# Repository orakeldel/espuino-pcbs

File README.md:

PCBs for espuino.

Note: Work in progress, no working prototyp yet.

Mainboard:
- Board with esp32 wrover, connectors for 6 buttons and led ring, lifepo battery charger, speaker (mono+stereo) and headphones.

Capabutton:
- Capacitive button with led and solder connector

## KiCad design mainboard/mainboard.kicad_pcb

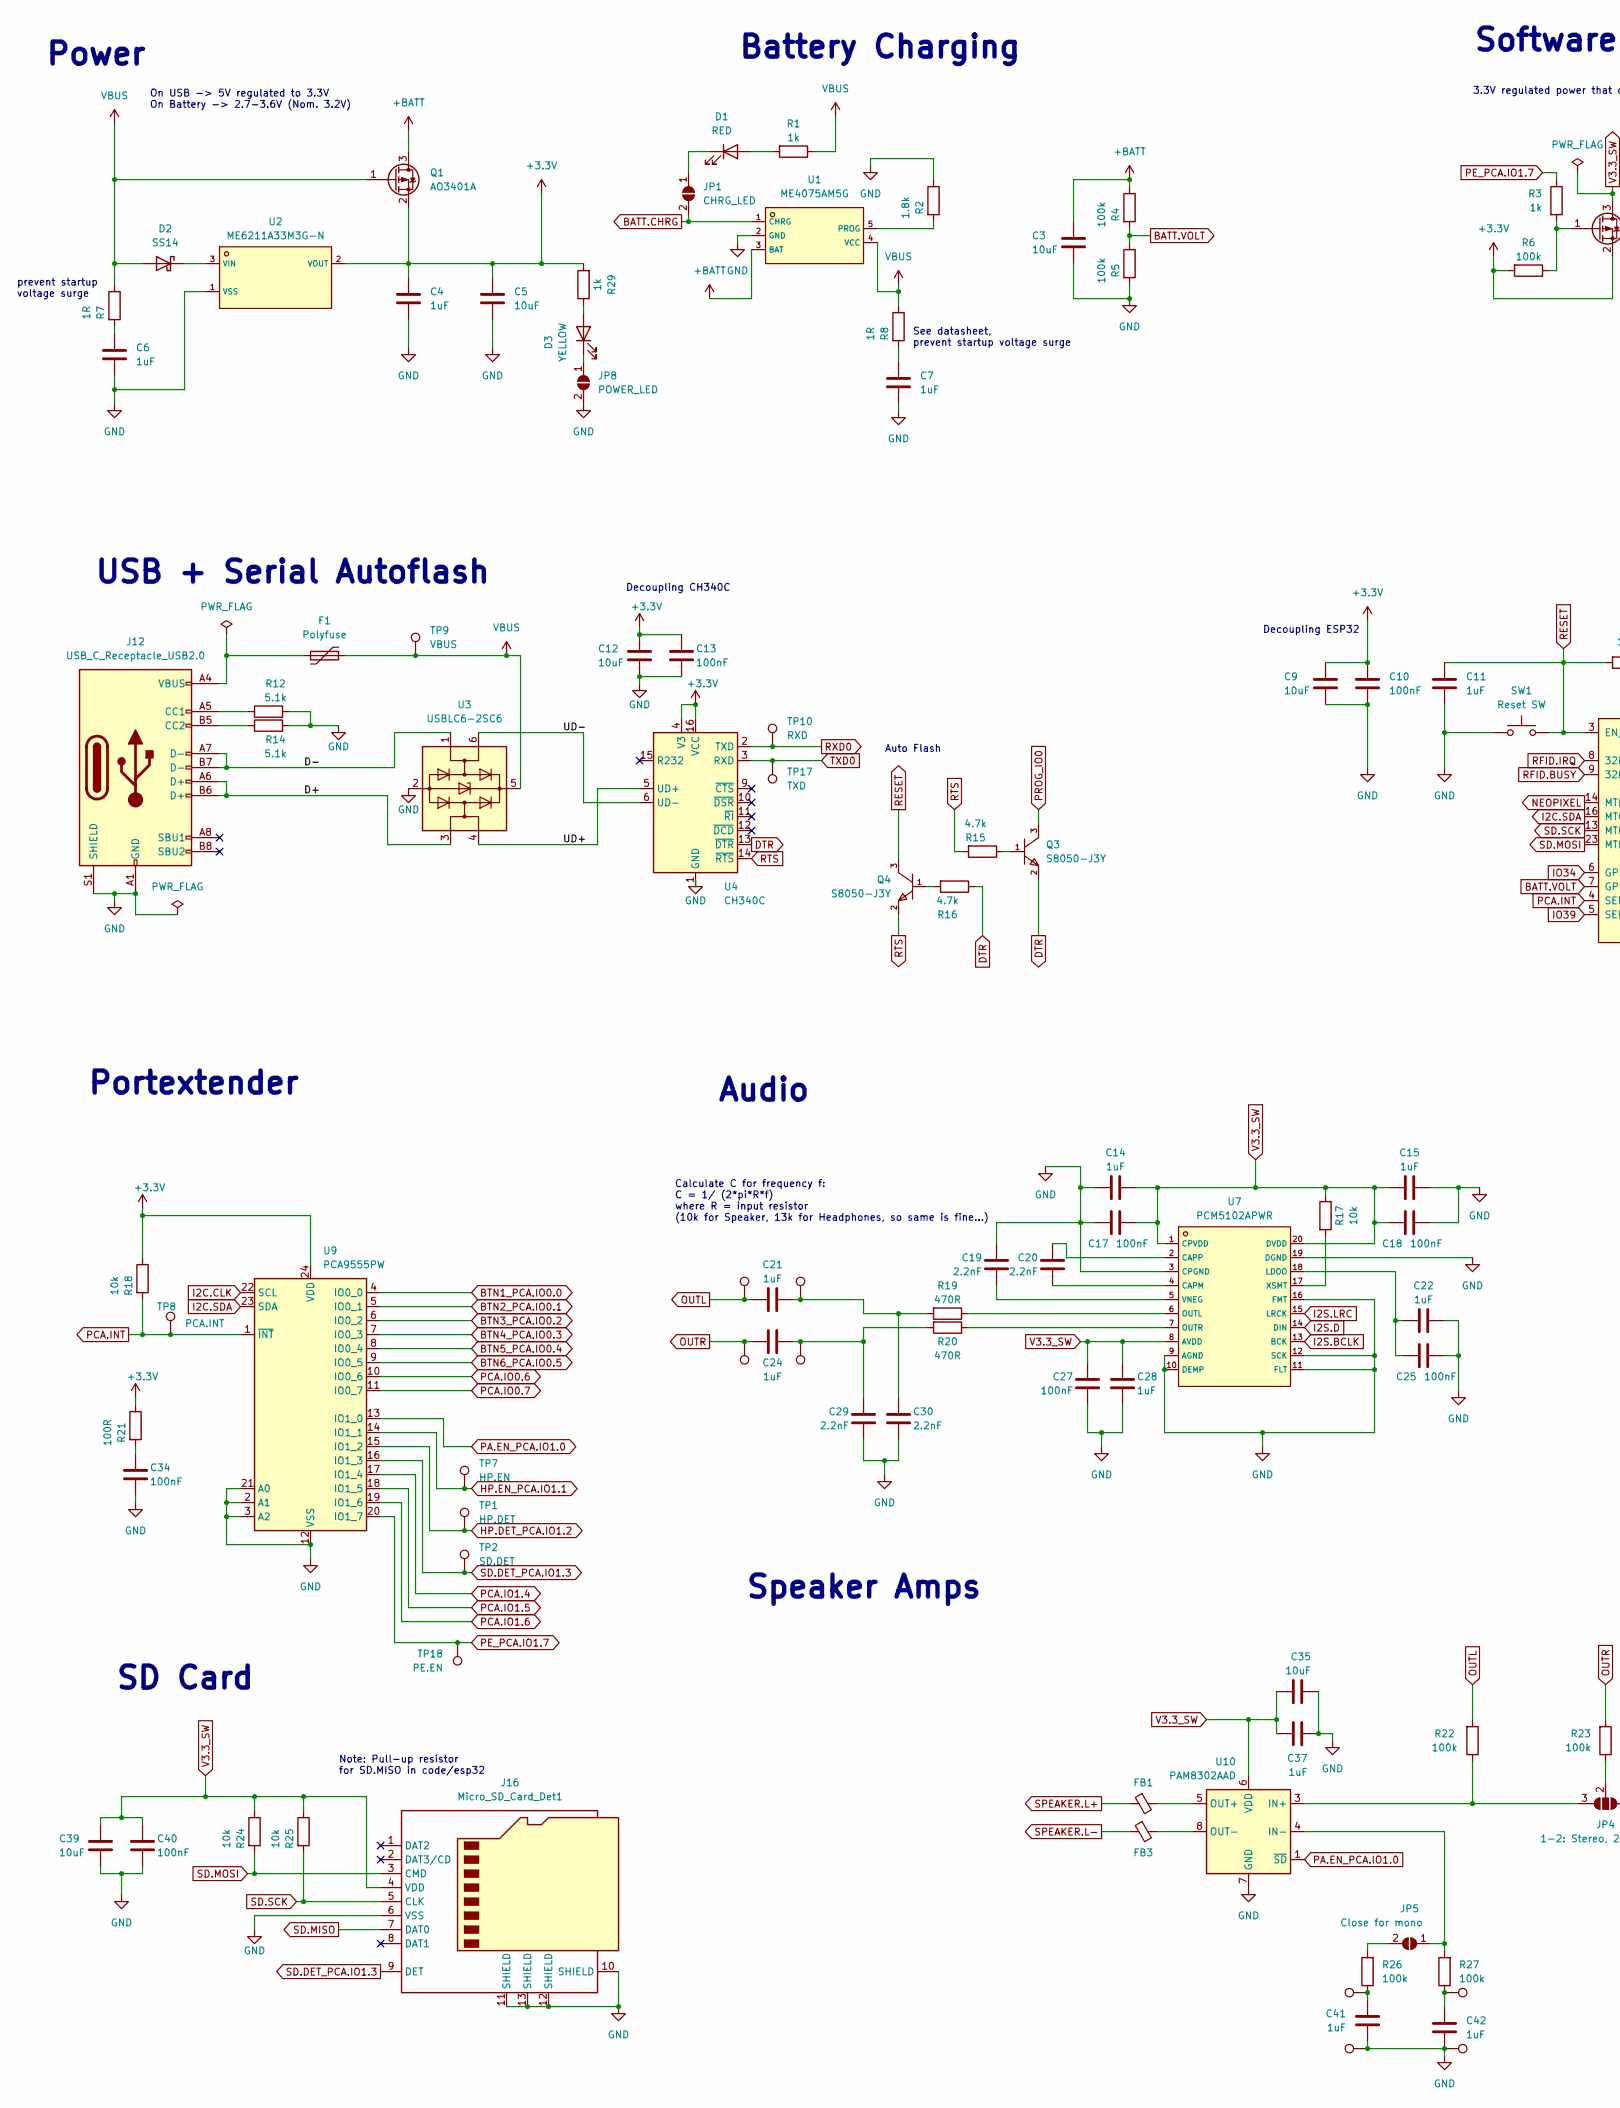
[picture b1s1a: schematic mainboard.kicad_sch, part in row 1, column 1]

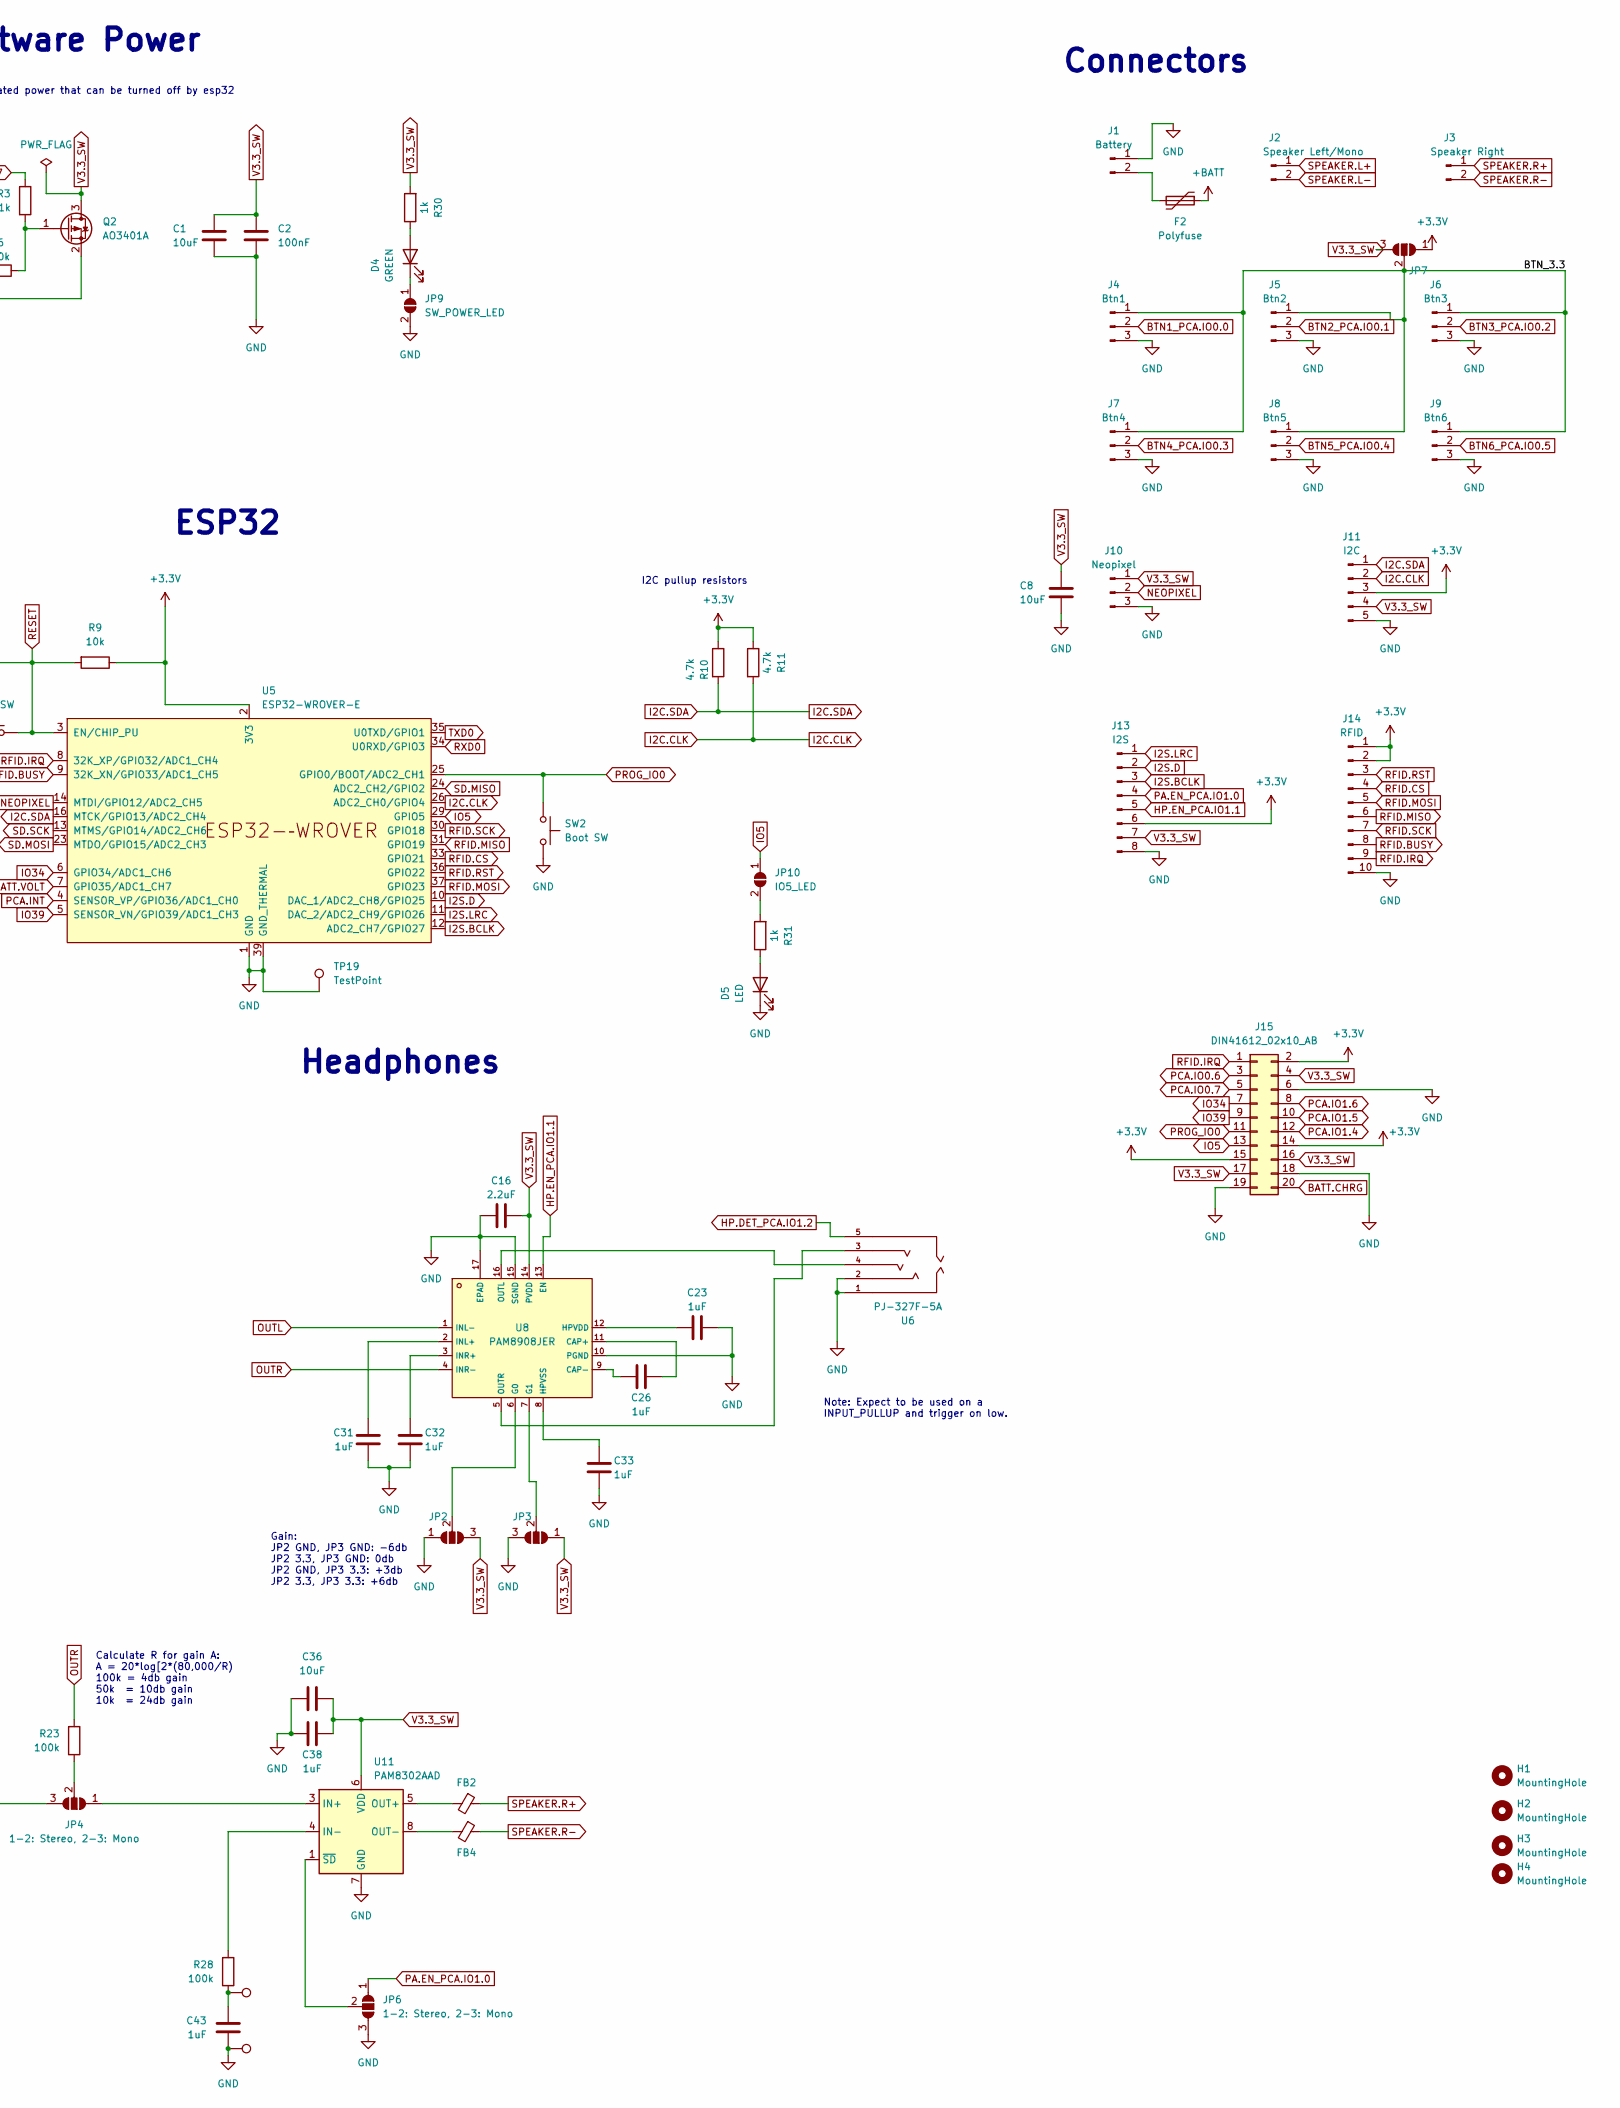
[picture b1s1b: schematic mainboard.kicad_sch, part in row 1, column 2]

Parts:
C1, C3, C5, C8, C9, C12, C35, C36, C39: 10uF; C_0603_1608Metric; LCSC C19702
C2, C10, C13, C17, C18, C25, C27, C34, C40: 100nF; C_0402_1005Metric; LCSC C1525
C4, C6, C7, C11, C14, C15, C21, C22, C23, C24, C26, C28, C31, C32, C33, C37, C38, C41, C42, C43: 1uF; C_0603_1608Metric; LCSC C15849
C16: 2.2uF; C_0603_1608Metric; LCSC C23630
C19, C20, C29, C30: 2.2nF; C_0603_1608Metric; LCSC C1604
D1: RED; LED_0805_2012Metric; LCSC C84256
D2: SS14; D_SMA; LCSC C8678
D3: YELLOW; LED_0805_2012Metric; LCSC C2296
D4: GREEN; LED_0805_2012Metric; LCSC C2297
D5: LED; LED_0805_2012Metric; LCSC C84256
F1, F2: Polyfuse; Fuse_0805_2012Metric; LCSC C70158
FB1, FB2, FB3, FB4: L_0603_1608Metric; LCSC C1002
H1, H2, H3, H4: MountingHole; MountingHole_3.2mm_M3_DIN965_Pad_TopOnly
J1: Battery; JST_XH_B2B-XH-A_1x02_P2.50mm_Vertical
J2: Speaker Left/Mono; TerminalBlock_Phoenix_PT-1,5-2-5.0-H_1x02_P5.00mm_Horizontal
J3: Speaker Right; TerminalBlock_Phoenix_PT-1,5-2-5.0-H_1x02_P5.00mm_Horizontal
J4: Btn1; JST_PH_B3B-PH-K_1x03_P2.00mm_Vertical
J5: Btn2; JST_PH_B3B-PH-K_1x03_P2.00mm_Vertical
J6: Btn3; JST_PH_B3B-PH-K_1x03_P2.00mm_Vertical
J7: Btn4; JST_PH_B3B-PH-K_1x03_P2.00mm_Vertical
J8: Btn5; JST_PH_B3B-PH-K_1x03_P2.00mm_Vertical
J9: Btn6; JST_PH_B3B-PH-K_1x03_P2.00mm_Vertical
J10: Neopixel; JST_PH_B3B-PH-K_1x03_P2.00mm_Vertical
J11: I2C; PinHeader_1x05_P2.54mm_Vertical
J12: USB_C_Receptacle_USB2.0; USB_C_Receptacle_HRO_TYPE-C-31-M-12; LCSC C165948
J13: I2S; PinHeader_1x08_P2.54mm_Vertical
J14: RFID; PinHeader_1x10_P2.54mm_Vertical
J15: DIN41612_02x10_AB; PinHeader_2x10_P2.54mm_Vertical
J16: Micro_SD_Card_Det1; TF-SMD_TF-115; LCSC C266620
JP1: CHRG_LED; SolderJumper-2_P1.3mm_Open_RoundedPad1.0x1.5mm
JP2, JP3, JP7: SolderJumper-3_P1.3mm_Open_RoundedPad1.0x1.5mm
JP4, JP6: 1-2: Stereo, 2-3: Mono; SolderJumper-3_P1.3mm_Open_RoundedPad1.0x1.5mm
JP5: Close for mono; SolderJumper-2_P1.3mm_Open_RoundedPad1.0x1.5mm
JP8: POWER_LED; SolderJumper-2_P1.3mm_Open_RoundedPad1.0x1.5mm
JP9: SW_POWER_LED; SolderJumper-2_P1.3mm_Open_RoundedPad1.0x1.5mm
JP10: IO5_LED; SolderJumper-2_P1.3mm_Open_RoundedPad1.0x1.5mm
Q1, Q2: AO3401A; SOT-23; LCSC C15127
Q3, Q4: S8050-J3Y; SOT-23-3_L3.0-W1.7-P0.95-LS2.9-BR; LCSC C364312
R1, R29, R30, R31: 1k; R_0402_1005Metric; LCSC C11702
R2: 1.8k; R_0805_2012Metric_Pad1.20x1.40mm_HandSolder; LCSC C17398
R3: 1k; R_0603_1608Metric; LCSC C21190
R4, R5, R6: 100k; R_0603_1608Metric; LCSC C25803
R7, R8: 1R; R_0603_1608Metric; LCSC C22936
R9, R17, R18: 10k; R_0402_1005Metric; LCSC C25744
R10, R11: 4.7k; R_0603_1608Metric; LCSC C23162
R12, R14: 5.1k; R_0402_1005Metric; LCSC C25905
R15, R16: 4.7k; R_0402_1005Metric; LCSC C25900
R19, R20: 470R; R_0805_2012Metric_Pad1.20x1.40mm_HandSolder; LCSC C17710
R21: 100R; R_0805_2012Metric_Pad1.20x1.40mm_HandSolder; LCSC C17408
R22, R23, R26, R27, R28: 100k; R_0805_2012Metric_Pad1.20x1.40mm_HandSolder; LCSC C149504
R24, R25: 10k; R_0603_1608Metric; LCSC C25804
SW1: Reset SW; SW_PUSH_6mm
SW2: Boot SW; SW_PUSH_6mm
TP1: HP.DET; TestPoint_THTPad_D1.5mm_Drill0.7mm
TP2: SD.DET; TestPoint_THTPad_D1.5mm_Drill0.7mm
TP3, TP4, TP5, TP6, TP11, TP12, TP13, TP14, TP15, TP16: TestPoint; TestPoint_THTPad_D1.5mm_Drill0.7mm
TP7: HP.EN; TestPoint_THTPad_D1.5mm_Drill0.7mm
TP8: PCA.INT; TestPoint_THTPad_D1.5mm_Drill0.7mm
TP9: VBUS; TestPoint_Pad_D1.5mm
TP10: RXD; TestPoint_Pad_D1.5mm
TP17: TXD; TestPoint_Pad_D1.5mm
TP18: PE.EN; TestPoint_THTPad_D1.5mm_Drill0.7mm
TP19: TestPoint; TestPoint_THTPad_3.0x3.0mm_Drill1.5mm
U1: ME4075AM5G; SOT-23-5_L2.9-W1.6-P0.95-LS2.8-BL; LCSC C558564
U2: ME6211A33M3G-N; SOT-23-3_L2.9-W1.6-P1.90-LS2.8-BR; LCSC C168807
U3: USBLC6-2SC6; SOT-23-6; LCSC C2827654
U4: CH340C; SOIC-16_3.9x9.9mm_P1.27mm; LCSC C7464026
U5: ESP32-WROVER-E; LCSC C701352
U6: PJ-327F-5A; AUDIO-SMD_PJ-327F-5A; LCSC C128989
U7: PCM5102APWR; TSSOP-20_L6.5-W4.4-P0.65-LS6.4-BL; LCSC C107671
U8: PAM8908JER; QFN-16_L3.0-W3.0-P0.50-BL-EP1.7; LCSC C33233
U9: PCA9555PW; TSSOP-24_4.4x7.8mm_P0.65mm; LCSC C128392
U10, U11: PAM8302AAD; SOP-8_L4.9-W3.9-P1.27-LS6.0-BL; LCSC C112137

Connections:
+3.3V: C4.1, C5.1, C9.1, C10.1, C12.1, C13.1, J11.3, J13.6, J14.1, J14.2, J15.2, J15.14, J15.15, JP7.1 (A), Q1.2 (S), Q2.2 (S), R6.2, R9.1, R10.1, R11.1, R18.1, R21.1, R29.2, U2.2 (VOUT), U4.4 (V3), U4.16 (VCC), U5.2 (3V3), U9.24 (VDD)
+BATT: C3.1, F2.1, Q1.3 (D), R4.1, U1.3 (BAT)
/BTN_3.3: J4.1, J5.1, J6.1, J7.1, J8.1, J9.1, JP7.2 (C)
/D+: J12.A6 (D+), J12.B6 (D+), U3.3 (I/O2)
/D-: J12.A7 (D-), J12.B7 (D-), U3.1 (I/O1)
/UD+: U3.4 (I/O2), U4.5 (UD+)
/UD-: U3.6 (I/O1), U4.6 (UD-)
BATT.CHRG: J15.20, JP1.2 (B), U1.1 (CHRG)
BATT.VOLT: R4.2, R5.1, U5.7 (GPIO35/ADC1_CH7)
BTN1_PCA.IO0.0: J4.2, U9.4 (IO0_0)
BTN2_PCA.IO0.1: J5.2, U9.5 (IO0_1)
BTN3_PCA.IO0.2: J6.2, U9.6 (IO0_2)
BTN4_PCA.IO0.3: J7.2, U9.7 (IO0_3)
BTN5_PCA.IO0.4: J8.2, U9.8 (IO0_4)
BTN6_PCA.IO0.5: J9.2, U9.9 (IO0_5)
DTR: Q3.2 (E), R16.1, U4.13 (~DTR)
GND: C1.2, C2.2, C3.2, C4.2, C5.2, C6.2, C7.2, C8.2, C9.2, C10.2, C11.2, C12.2, C13.2, C14.1, C15.2, C16.2, C17.1, C18.2, C19.2, C22.2, C23.2, C25.2, C27.2, C28.2, C29.1, C30.1, C31.2, C32.2, C33.2, C34.2, C35.2, C36.2, C37.2, C38.2, C39.2, C40.2, C41.2, C42.2, C43.2, D5.1 (K), J1.1, J4.3, J5.3, J6.3, J7.3, J8.3, J9.3, J10.3, J11.5, J12.A1 (GND), J12.A12 (GND), J12.B1 (GND), J12.B12 (GND), J12.S1 (SHIELD), J13.8, J14.10, J15.6, J15.18, J15.19, J16.6 (VSS), J16.10 (SHIELD), J16.11 (SHIELD), J16.12 (SHIELD), J16.13 (SHIELD), JP2.1 (A), JP3.3 (B), JP6.3 (B), JP8.2 (B), JP9.2 (B), R2.1, R5.2, R12.2, R14.2, SW1.1, SW2.2, TP14.1, TP15.1, TP16.1, TP19.1, U1.2 (GND), U2.1 (VSS), U3.2 (GND), U4.1 (GND), U5.1 (GND), U5.15 (GND), U5.38 (GND), U5.39 (GND_THERMAL), U6.1 (GND(MIC)), U6.2 (MIC(GND)), U7.3 (CPGND), U7.9 (AGND), U7.10 (DEMP), U7.11 (FLT), U7.12 (SCK), U7.16 (FMT), U7.19 (DGND), U8.10 (PGND), U8.15 (SGND), U8.17 (EPAD), U9.2 (A1), U9.3 (A2), U9.12 (VSS), U9.21 (A0), U10.7 (GND), U11.7 (GND)
HP.DET_PCA.IO1.2: TP1.1, U6.5 (DETECT), U9.15 (IO1_2)
HP.EN_PCA.IO1.1: J13.5, TP7.1, U8.13 (EN), U9.14 (IO1_1)
I2C.CLK: J11.2, R11.2, U5.26 (ADC2_CH0/GPIO4), U9.22 (SCL)
I2C.SDA: J11.1, R10.2, U5.16 (MTCK/GPIO13/ADC2_CH4), U9.23 (SDA)
I2S.BCLK: J13.3, U5.12 (ADC2_CH7/GPIO27), U7.13 (BCK)
I2S.D: J13.2, U5.10 (DAC_1/ADC2_CH8/GPIO25), U7.14 (DIN)
I2S.LRC: J13.1, U5.11 (DAC_2/ADC2_CH9/GPIO26), U7.15 (LRCK)
IO5: J15.13, JP10.1 (A), U5.29 (GPIO5)
IO34: J15.7, U5.6 (GPIO34/ADC1_CH6)
IO39: J15.9, U5.5 (SENSOR_VN/GPIO39/ADC1_CH3)
NEOPIXEL: J10.2, U5.14 (MTDI/GPIO12/ADC2_CH5)
unnamed: C6.1, R7.2
unnamed: C7.1, R8.2
unnamed: C21.2, C30.2, R19.2, TP4.1
unnamed: C24.2, C29.2, R20.2, TP6.1
unnamed: C34.1, R21.2
unnamed: C41.1, R26.1, TP11.1
unnamed: C42.1, R27.1, TP12.1
unnamed: C43.1, R28.1, TP13.1
unnamed: D1.2 (A), R1.2
unnamed: D1.1 (K), JP1.1 (A)
unnamed: D2.1 (K), U2.3 (VIN)
unnamed: D3.2 (A), R29.1
unnamed: D3.1 (K), JP8.1 (A)
unnamed: D4.2 (A), R30.1
unnamed: D4.1 (K), JP9.1 (A)
unnamed: D5.2 (A), R31.1
unnamed: F1.2, J12.A4 (VBUS), J12.A9 (VBUS), J12.B4 (VBUS), J12.B9 (VBUS)
unnamed: F2.2, J1.2
unnamed: J12.A5 (CC1), R12.1
unnamed: J12.B5 (CC2), R14.1
unnamed: JP2.2 (C), U8.6 (G0)
unnamed: JP3.2 (C), U8.7 (G1)
unnamed: JP4.1 (A), U11.3 (IN+)
unnamed: JP4.3 (B), R22.1, U10.3 (IN+)
unnamed: JP4.2 (C), R23.1
unnamed: JP5.1 (A), R27.2, U10.4 (IN-)
unnamed: JP5.2 (B), R26.2
unnamed: JP6.2 (C), U11.1 (~SD)
unnamed: JP10.2 (B), R31.2
unnamed: Q2.1 (G), R3.2, R6.1
unnamed: Q3.1 (B), R15.1
unnamed: Q4.1 (B), R16.2
unnamed: R2.2, U1.5 (PROG)
unnamed: U6.4 (LET), U8.16 (OUTL)
unnamed: U6.3 (RT), U8.5 (OUTR)
unnamed: C20.1, U7.4 (CAPM)
unnamed: C20.2, U7.2 (CAPP)
unnamed: C22.1, C25.1, U7.18 (LDOO)
unnamed: R19.1, U7.6 (OUTL)
unnamed: R20.1, U7.7 (OUTR)
unnamed: C19.1, U7.5 (VNEG)
unnamed: R17.2, U7.17 (XSMT)
unnamed: C26.2, U8.11 (CAP+)
unnamed: C26.1, U8.9 (CAP-)
unnamed: C23.1, U8.12 (HPVDD)
unnamed: C33.1, U8.8 (HPVSS)
unnamed: C31.1, U8.2 (INL+)
unnamed: C32.1, U8.3 (INR+)
unnamed: FB1.2, U10.5 (OUT+)
unnamed: FB3.2, U10.8 (OUT-)
unnamed: R28.2, U11.4 (IN-)
unnamed: FB2.2, U11.5 (OUT+)
unnamed: FB4.2, U11.8 (OUT-)
OUTL: C21.1, R22.2, TP3.1, U8.1 (INL-)
OUTR: C24.1, R23.2, TP5.1, U8.4 (INR-)
PA.EN_PCA.IO1.0: J13.4, JP6.1 (A), U9.13 (IO1_0), U10.1 (~SD)
PCA.INT: R18.2, TP8.1, U5.4 (SENSOR_VP/GPIO36/ADC1_CH0), U9.1 (~INT)
PCA.IO0.6: J15.3, U9.10 (IO0_6)
PCA.IO0.7: J15.5, U9.11 (IO0_7)
PCA.IO1.4: J15.12, U9.17 (IO1_4)
PCA.IO1.5: J15.10, U9.18 (IO1_5)
PCA.IO1.6: J15.8, U9.19 (IO1_6)
PE_PCA.IO1.7: R3.1, TP18.1, U9.20 (IO1_7)
PROG_IO0: J15.11, Q3.3 (C), SW2.1, U5.25 (GPIO0/BOOT/ADC2_CH1)
RESET: C11.1, Q4.3 (C), R9.2, SW1.2, U5.3 (EN/CHIP_PU)
RFID.BUSY: J14.8, U5.9 (32K_XN/GPIO33/ADC1_CH5)
RFID.CS: J14.4, U5.33 (GPIO21)
RFID.IRQ: J14.9, J15.1, U5.8 (32K_XP/GPIO32/ADC1_CH4)
RFID.MISO: J14.6, U5.31 (GPIO19)
RFID.MOSI: J14.5, U5.37 (GPIO23)
RFID.RST: J14.3, U5.36 (GPIO22)
RFID.SCK: J14.7, U5.30 (GPIO18)
RTS: Q4.2 (E), R15.2, U4.14 (~RTS)
RXD0: TP10.1, U4.2 (TXD), U5.34 (U0RXD/GPIO3)
SD.DET_PCA.IO1.3: J16.9 (DET), TP2.1, U9.16 (IO1_3)
SD.MISO: J16.7 (DAT0), U5.24 (ADC2_CH2/GPIO2)
SD.MOSI: J16.3 (CMD), R24.2, U5.23 (MTDO/GPIO15/ADC2_CH3)
SD.SCK: J16.5 (CLK), R25.2, U5.13 (MTMS/GPIO14/ADC2_CH6)
SPEAKER.L+: FB1.1, J2.1
SPEAKER.L-: FB3.1, J2.2
SPEAKER.R+: FB2.1, J3.1
SPEAKER.R-: FB4.1, J3.2
TXD0: TP17.1, U4.3 (RXD), U5.35 (U0TXD/GPIO1)
V3.3_SW: C1.1, C2.1, C8.1, C14.2, C15.1, C16.1, C17.2, C18.1, C27.1, C28.1, C35.1, C36.1, C37.1, C38.1, C39.1, C40.1, J10.1, J11.4, J13.7, J15.4, J15.16, J15.17, J16.4 (VDD), JP2.3 (B), JP3.1 (A), JP7.3 (B), Q2.3 (D), R17.1, R24.1, R25.1, R30.2, U7.1 (CPVDD), U7.8 (AVDD), U7.20 (DVDD), U8.14 (PVDD), U10.6 (VDD), U11.6 (VDD)
VBUS: D2.2 (A), F1.1, Q1.1 (G), R1.1, R7.1, R8.1, TP9.1, U1.4 (VCC), U3.5 (VBUS)

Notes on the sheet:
Decoupling ESP32
ESP32
Gain: JP2 GND, JP3 GND: -6db JP2 3.3, JP3 GND: 0db JP2 GND, JP3 3.3: +3db JP2 3.3, JP3 3.3: +6db
Decoupling CH340C
Connectors
Note: Pull-up resistor for SD.MISO in code/esp32
Headphones
Audio
Software Power
Speaker Amps
3.3V regulated power that can be turned off by esp32
Note: Expect to be used on a INPUT_PULLUP and trigger on low.
Calculate C for frequency f: C = 1/ (2*pi*R*f) where R = input resistor (10k for Speaker, 13k for Headphones, so same is fine...)
Power
See datasheet, prevent startup voltage surge
I2C pullup resistors
prevent startup voltage surge
SD Card
Battery Charging
Auto Flash
USB + Serial Autoflash
Calculate R for gain A: A = 20*log[2*(80,000/R) 100k = 4db gain 50k = 10db gain 10k = 24db gain
On USB -> 5V regulated to 3.3V On Battery -> 2.7-3.6V (Nom. 3.2V)
Portextender

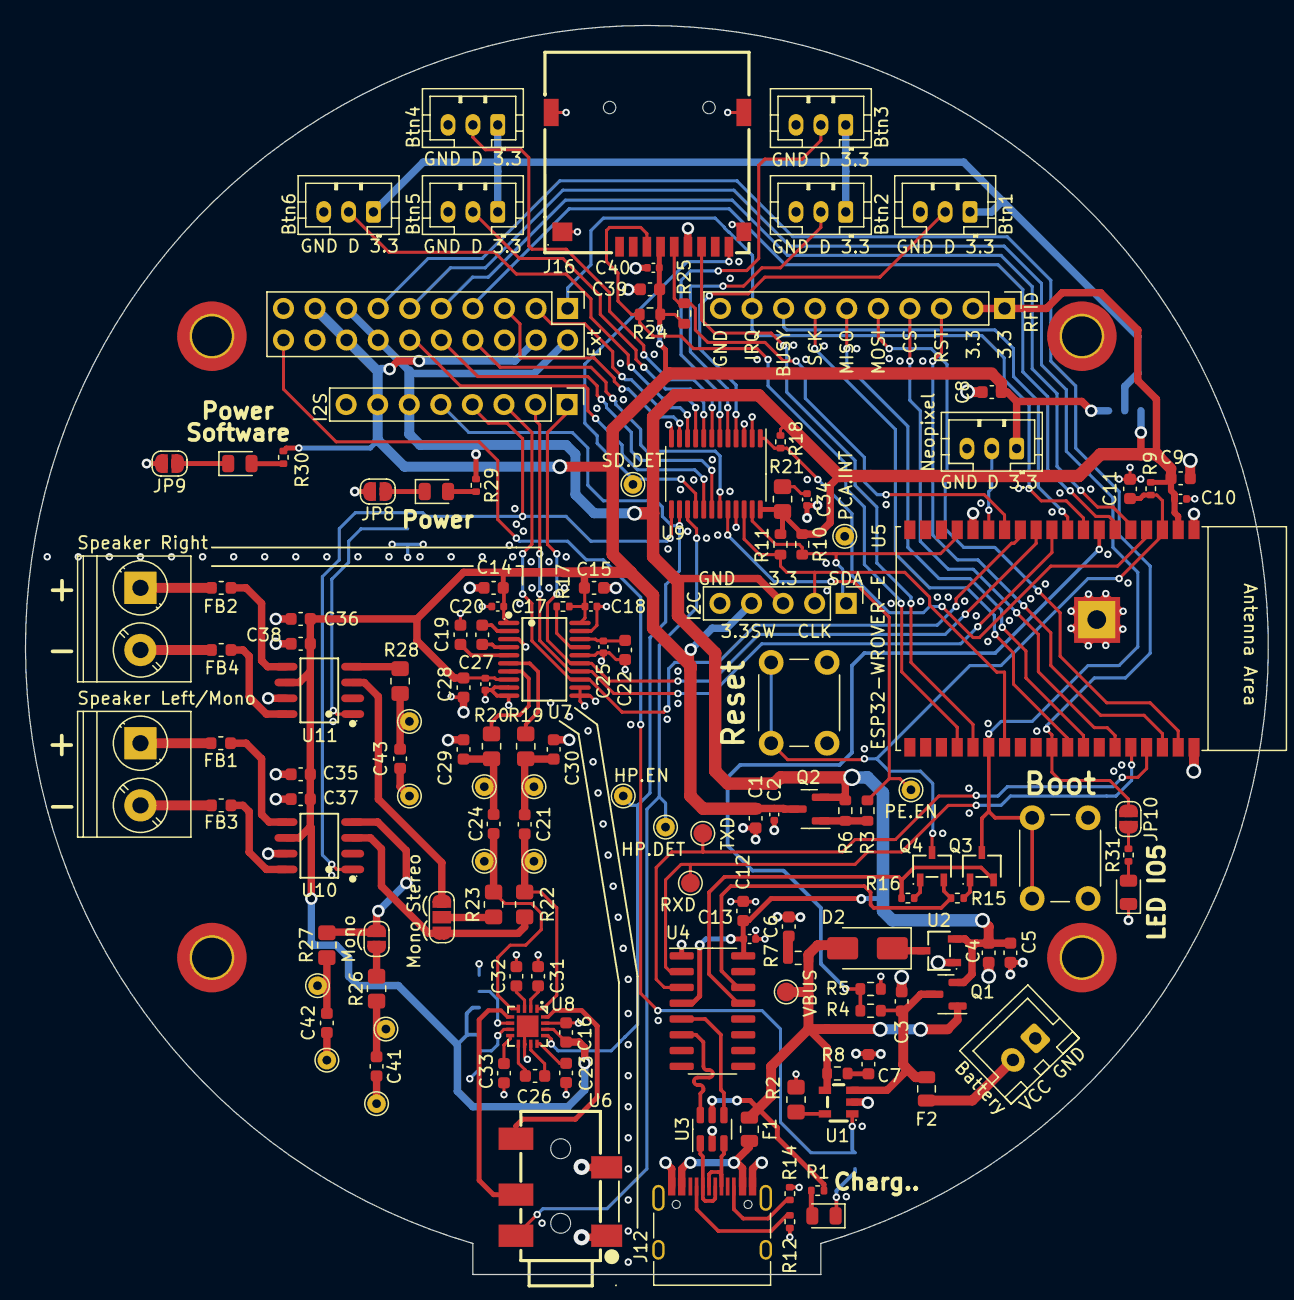
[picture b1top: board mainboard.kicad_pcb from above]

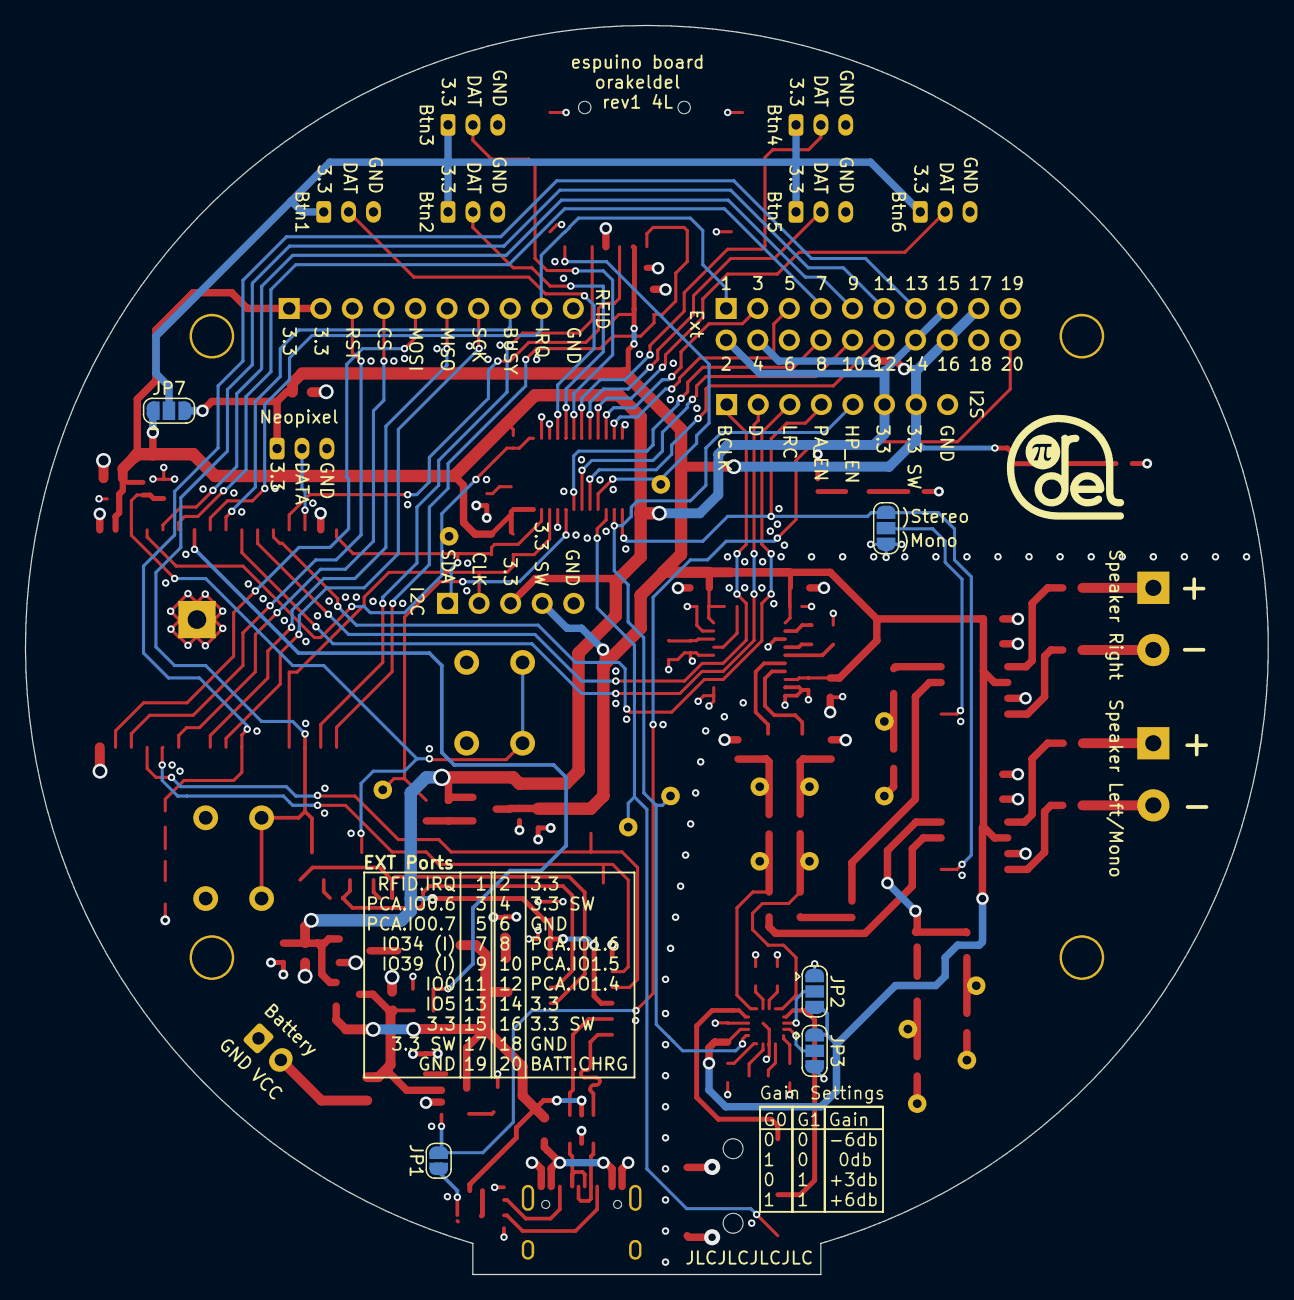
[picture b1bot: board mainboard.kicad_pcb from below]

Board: 4 copper layers, 100.0 x 100.5 mm, 150 parts (5 on the bottom side), 113 nets.

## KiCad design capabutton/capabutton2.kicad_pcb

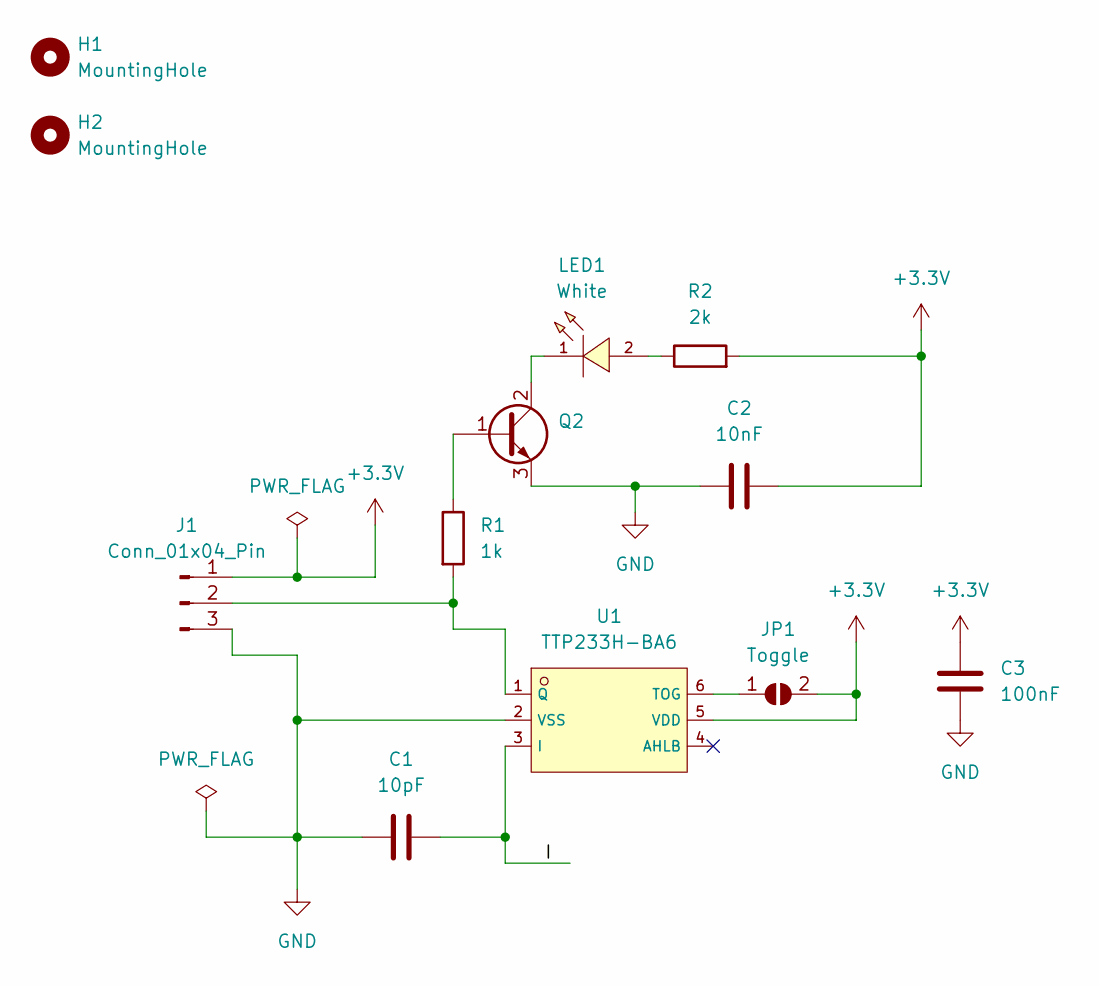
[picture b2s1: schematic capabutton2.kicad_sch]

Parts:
C1: 10pF; C0402; LCSC C32949
C2: 10nF; C0402; LCSC C15195
C3: 100nF; C0402; LCSC C1525
H1, H2: MountingHole; MountingHole_2.2mm_M2
J1: Conn_01x04_Pin; SolderConnector 3x1mm 03x01
JP1: Toggle; SolderJumper-2_P1.3mm_Open_RoundedPad1.0x1.5mm
LED1: White; LED-SMD_L3.2-W1.6-RD-EH_WHITE; LCSC C3646935
Q2: SOT-23-3_L2.9-W1.3-P1.90-LS2.4-BR; LCSC C2145
R1: 1k; R0402; LCSC C11702
R2: 2k; R0402; LCSC C4109
U1: TTP233H-BA6; SOT-23-6_L2.9-W1.7-P0.95-LS2.8-BL; LCSC C2890349

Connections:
+3.3V: C2.1, C3.2, J1.1, JP1.2 (B), R2.2, U1.5 (VDD)
/I: C1.1, U1.3 (I)
GND: C1.2, C2.2, C3.1, J1.3, Q2.3 (E), U1.2 (VSS)
unnamed: J1.2, R1.2, U1.1 (Q)
unnamed: JP1.1 (A), U1.6 (TOG)
unnamed: LED1.2 (+), R2.1
unnamed: LED1.1 (-), Q2.2 (C)
unnamed: Q2.1 (B), R1.1

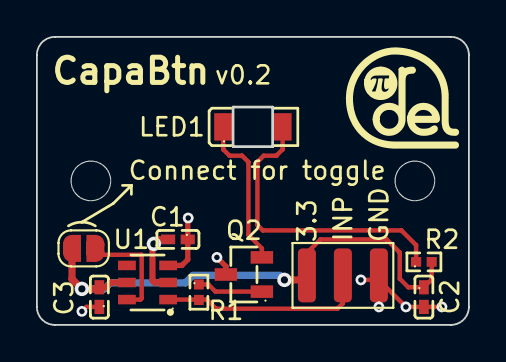
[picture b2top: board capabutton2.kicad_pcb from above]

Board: 2 copper layers, 24.0 x 16.0 mm, 12 parts (0 on the bottom side), 8 nets.
